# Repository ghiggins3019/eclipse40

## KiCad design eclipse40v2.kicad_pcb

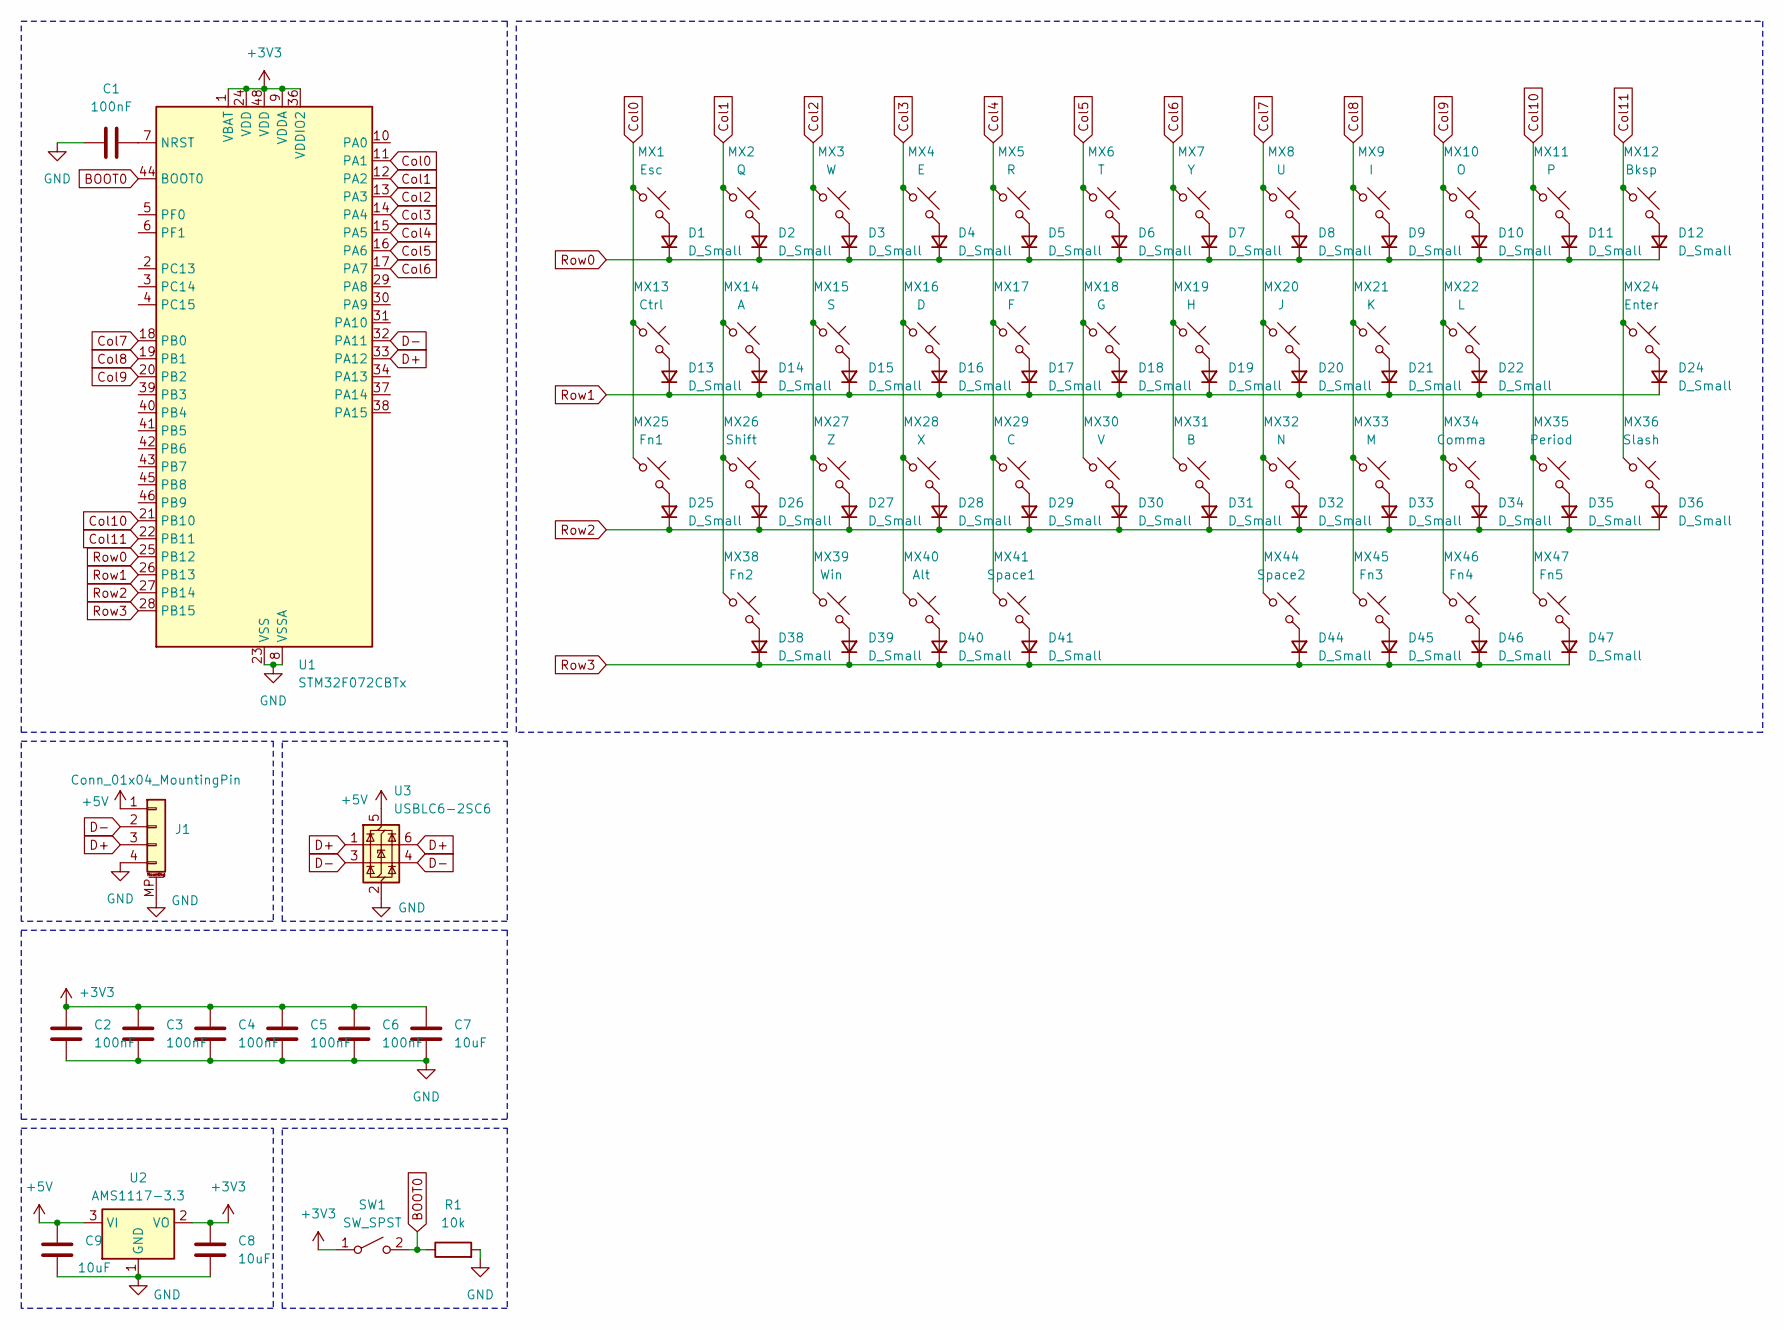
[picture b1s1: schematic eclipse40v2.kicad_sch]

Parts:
C1, C2, C3, C4, C5, C6: 100nF; C_0805_2012Metric_Pad1.18x1.45mm_HandSolder
C7, C8, C9: 10uF; C_0805_2012Metric_Pad1.18x1.45mm_HandSolder
D1, D2, D3, D4, D5, D6, D7, D8, D9, D10, D11, D12, D13, D14, D15, D16, D17, D18, D19, D20, D21, D22, D24, D25, D26, D27, D28, D29, D30, D31, D32, D33, D34, D35, D36, D38, D39, D40, D41, D44, D45, D46, D47: D_Small; D_0805_2012Metric_Pad1.15x1.40mm_HandSolder
J1: Conn_01x04_MountingPin; Molex_Pico-EZmate_78171-0004_1x04-1MP_P1.20mm_Vertical
MX1: Esc; SW_MX_HS_CPG151101S11_1.5u
MX2: Q; SW_MX_HS_CPG151101S11_1u
MX3: W; SW_MX_HS_CPG151101S11_1u
MX4: E; SW_MX_HS_CPG151101S11_1u
MX5: R; SW_MX_HS_CPG151101S11_1u
MX6: T; SW_MX_HS_CPG151101S11_1u
MX7: Y; SW_MX_HS_CPG151101S11_1u
MX8: U; SW_MX_HS_CPG151101S11_1u
MX9: I; SW_MX_HS_CPG151101S11_1u
MX10: O; SW_MX_HS_CPG151101S11_1u
MX11: P; SW_MX_HS_CPG151101S11_1u
MX12: Bksp; SW_MX_HS_CPG151101S11_1.5u
MX13: Ctrl; SW_MX_HS_CPG151101S11_1.75u
MX14: A; SW_MX_HS_CPG151101S11_1u
MX15: S; SW_MX_HS_CPG151101S11_1u
MX16: D; SW_MX_HS_CPG151101S11_1u
MX17: F; SW_MX_HS_CPG151101S11_1u
MX18: G; SW_MX_HS_CPG151101S11_1u
MX19: H; SW_MX_HS_CPG151101S11_1u
MX20: J; SW_MX_HS_CPG151101S11_1u
MX21: K; SW_MX_HS_CPG151101S11_1u
MX22: L; SW_MX_HS_CPG151101S11_1u
MX24: Enter; SW_MX_HS_CPG151101S11_1u
MX25: Fn1; SW_MX_HS_CPG151101S11_1u
MX26: Shift; SW_MX_HS_CPG151101S11_1.25u
MX27: Z; SW_MX_HS_CPG151101S11_1u
MX28: X; SW_MX_HS_CPG151101S11_1u
MX29: C; SW_MX_HS_CPG151101S11_1u
MX30: V; SW_MX_HS_CPG151101S11_1u
MX31: B; SW_MX_HS_CPG151101S11_1u
MX32: N; SW_MX_HS_CPG151101S11_1u
MX33: M; SW_MX_HS_CPG151101S11_1u
MX34: Comma; SW_MX_HS_CPG151101S11_1u
MX35: Period; SW_MX_HS_CPG151101S11_1u
MX36: Slash; SW_MX_HS_CPG151101S11_1.75u
MX38: Fn2; SW_MX_HS_CPG151101S11_1u
MX39: Win; SW_MX_HS_CPG151101S11_1u
MX40: Alt; SW_MX_HS_CPG151101S11_1u
MX41: Space1; SW_MX_HS_CPG151101S11_1u
MX44: Space2; SW_MX_HS_CPG151101S11_1u
MX45: Fn3; SW_MX_HS_CPG151101S11_1u
MX46: Fn4; SW_MX_HS_CPG151101S11_1u
MX47: Fn5; SW_MX_HS_CPG151101S11_1u
R1: 10k; C_0805_2012Metric_Pad1.18x1.45mm_HandSolder
SW1: SW_SPST; SW_SPST_SKQG_WithStem
U1: STM32F072CBTx; LQFP-48_7x7mm_P0.5mm
U2: AMS1117-3.3; SOT-223-3_TabPin2
U3: USBLC6-2SC6; SOT-23-6

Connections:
+3V3: C2.2, C3.2, C4.2, C5.2, C6.2, C7.2, C8.1, SW1.1 (A), U1.1 (VBAT), U1.9 (VDDA), U1.24 (VDD), U1.36 (VDDIO2), U1.48 (VDD), U2.2 (VO)
+5V: C9.1, J1.1, U2.3 (VI), U3.5 (VBUS)
BOOT0: R1.1, SW1.2 (B), U1.44 (BOOT0)
Col0: MX1.1, MX13.1, MX25.1, U1.11 (PA1)
Col1: MX2.1, MX14.1, MX26.1, MX38.1, U1.12 (PA2)
Col2: MX3.1, MX15.1, MX27.1, MX39.1, U1.13 (PA3)
Col3: MX4.1, MX16.1, MX28.1, MX40.1, U1.14 (PA4)
Col4: MX5.1, MX17.1, MX29.1, MX41.1, U1.15 (PA5)
Col5: MX6.1, MX18.1, MX30.1, U1.16 (PA6)
Col6: MX7.1, MX19.1, MX31.1, U1.17 (PA7)
Col7: MX8.1, MX20.1, MX32.1, MX44.1, U1.18 (PB0)
Col8: MX9.1, MX21.1, MX33.1, MX45.1, U1.19 (PB1)
Col9: MX10.1, MX22.1, MX34.1, MX46.1, U1.20 (PB2)
Col10: MX11.1, MX35.1, MX47.1, U1.21 (PB10)
Col11: MX12.1, MX24.1, MX36.1, U1.22 (PB11)
D+: J1.3, U1.33 (PA12), U3.1 (I/O1), U3.6 (I/O1)
D-: J1.2, U1.32 (PA11), U3.3 (I/O2), U3.4 (I/O2)
GND: C1.1, C2.1, C3.1, C4.1, C5.1, C6.1, C7.1, C8.2, C9.2, J1.4, J1.MP (MountPin), R1.2, U1.8 (VSSA), U1.23 (VSS), U1.35 (VSS), U1.47 (VSS), U2.1 (GND), U3.2 (GND)
unnamed: D1.2 (A), MX1.2
unnamed: D2.2 (A), MX2.2
unnamed: D3.2 (A), MX3.2
unnamed: D4.2 (A), MX4.2
unnamed: D5.2 (A), MX5.2
unnamed: D6.2 (A), MX6.2
unnamed: D7.2 (A), MX7.2
unnamed: D8.2 (A), MX8.2
unnamed: D9.2 (A), MX9.2
unnamed: D10.2 (A), MX10.2
unnamed: D11.2 (A), MX11.2
unnamed: D12.2 (A), MX12.2
unnamed: D13.2 (A), MX13.2
unnamed: D14.2 (A), MX14.2
unnamed: D15.2 (A), MX15.2
unnamed: D16.2 (A), MX16.2
unnamed: D17.2 (A), MX17.2
unnamed: D18.2 (A), MX18.2
unnamed: D19.2 (A), MX19.2
unnamed: D20.2 (A), MX20.2
unnamed: D21.2 (A), MX21.2
unnamed: D22.2 (A), MX22.2
unnamed: D24.2 (A), MX24.2
unnamed: D25.2 (A), MX25.2
unnamed: D26.2 (A), MX26.2
unnamed: D27.2 (A), MX27.2
unnamed: D28.2 (A), MX28.2
unnamed: D29.2 (A), MX29.2
unnamed: D30.2 (A), MX30.2
unnamed: D31.2 (A), MX31.2
unnamed: D32.2 (A), MX32.2
unnamed: D33.2 (A), MX33.2
unnamed: D34.2 (A), MX34.2
unnamed: D35.2 (A), MX35.2
unnamed: D36.2 (A), MX36.2
unnamed: D38.2 (A), MX38.2
unnamed: D39.2 (A), MX39.2
unnamed: D40.2 (A), MX40.2
unnamed: D41.2 (A), MX41.2
unnamed: D44.2 (A), MX44.2
unnamed: D45.2 (A), MX45.2
unnamed: D46.2 (A), MX46.2
unnamed: D47.2 (A), MX47.2
unnamed: C1.2, U1.7 (NRST)
Row0: D1.1 (K), D2.1 (K), D3.1 (K), D4.1 (K), D5.1 (K), D6.1 (K), D7.1 (K), D8.1 (K), D9.1 (K), D10.1 (K), D11.1 (K), D12.1 (K), U1.25 (PB12)
Row1: D13.1 (K), D14.1 (K), D15.1 (K), D16.1 (K), D17.1 (K), D18.1 (K), D19.1 (K), D20.1 (K), D21.1 (K), D22.1 (K), D24.1 (K), U1.26 (PB13)
Row2: D25.1 (K), D26.1 (K), D27.1 (K), D28.1 (K), D29.1 (K), D30.1 (K), D31.1 (K), D32.1 (K), D33.1 (K), D34.1 (K), D35.1 (K), D36.1 (K), U1.27 (PB14)
Row3: D38.1 (K), D39.1 (K), D40.1 (K), D41.1 (K), D44.1 (K), D45.1 (K), D46.1 (K), D47.1 (K), U1.28 (PB15)

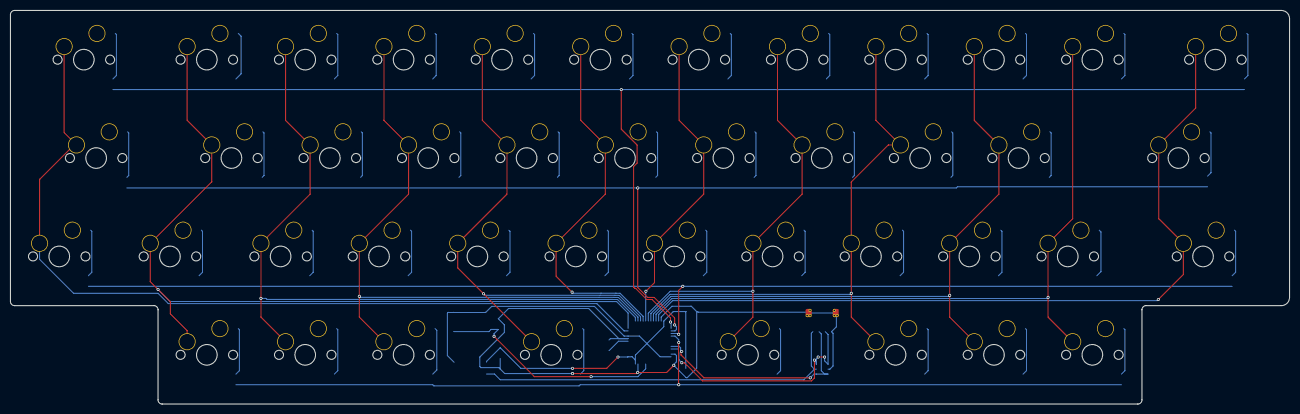
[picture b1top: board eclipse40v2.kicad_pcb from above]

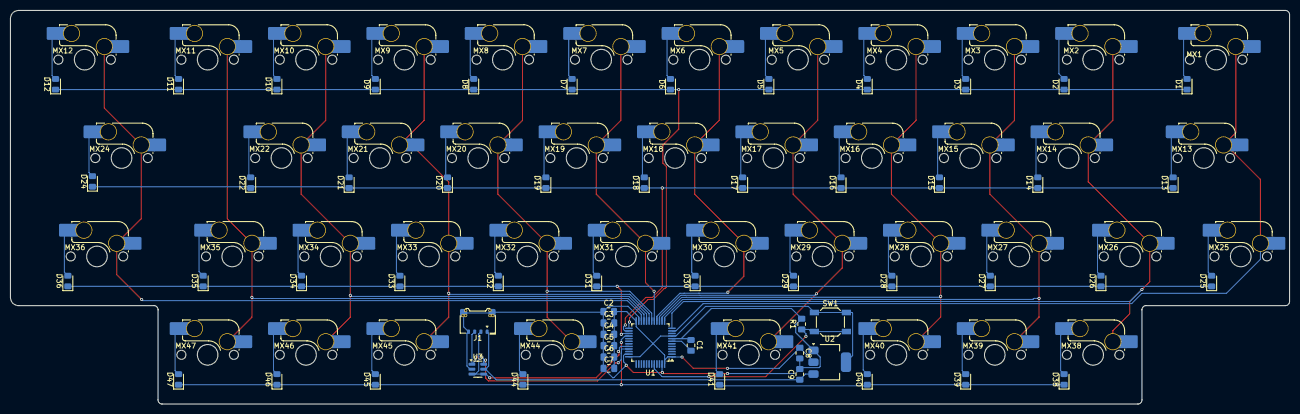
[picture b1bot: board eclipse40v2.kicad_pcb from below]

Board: 2 copper layers, 247.7 x 76.2 mm, 101 parts (101 on the bottom side), 66 nets.
